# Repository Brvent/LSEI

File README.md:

# LSEI
Aquest projecte tracta de dissenyar i implementar un controlador de motor ESR

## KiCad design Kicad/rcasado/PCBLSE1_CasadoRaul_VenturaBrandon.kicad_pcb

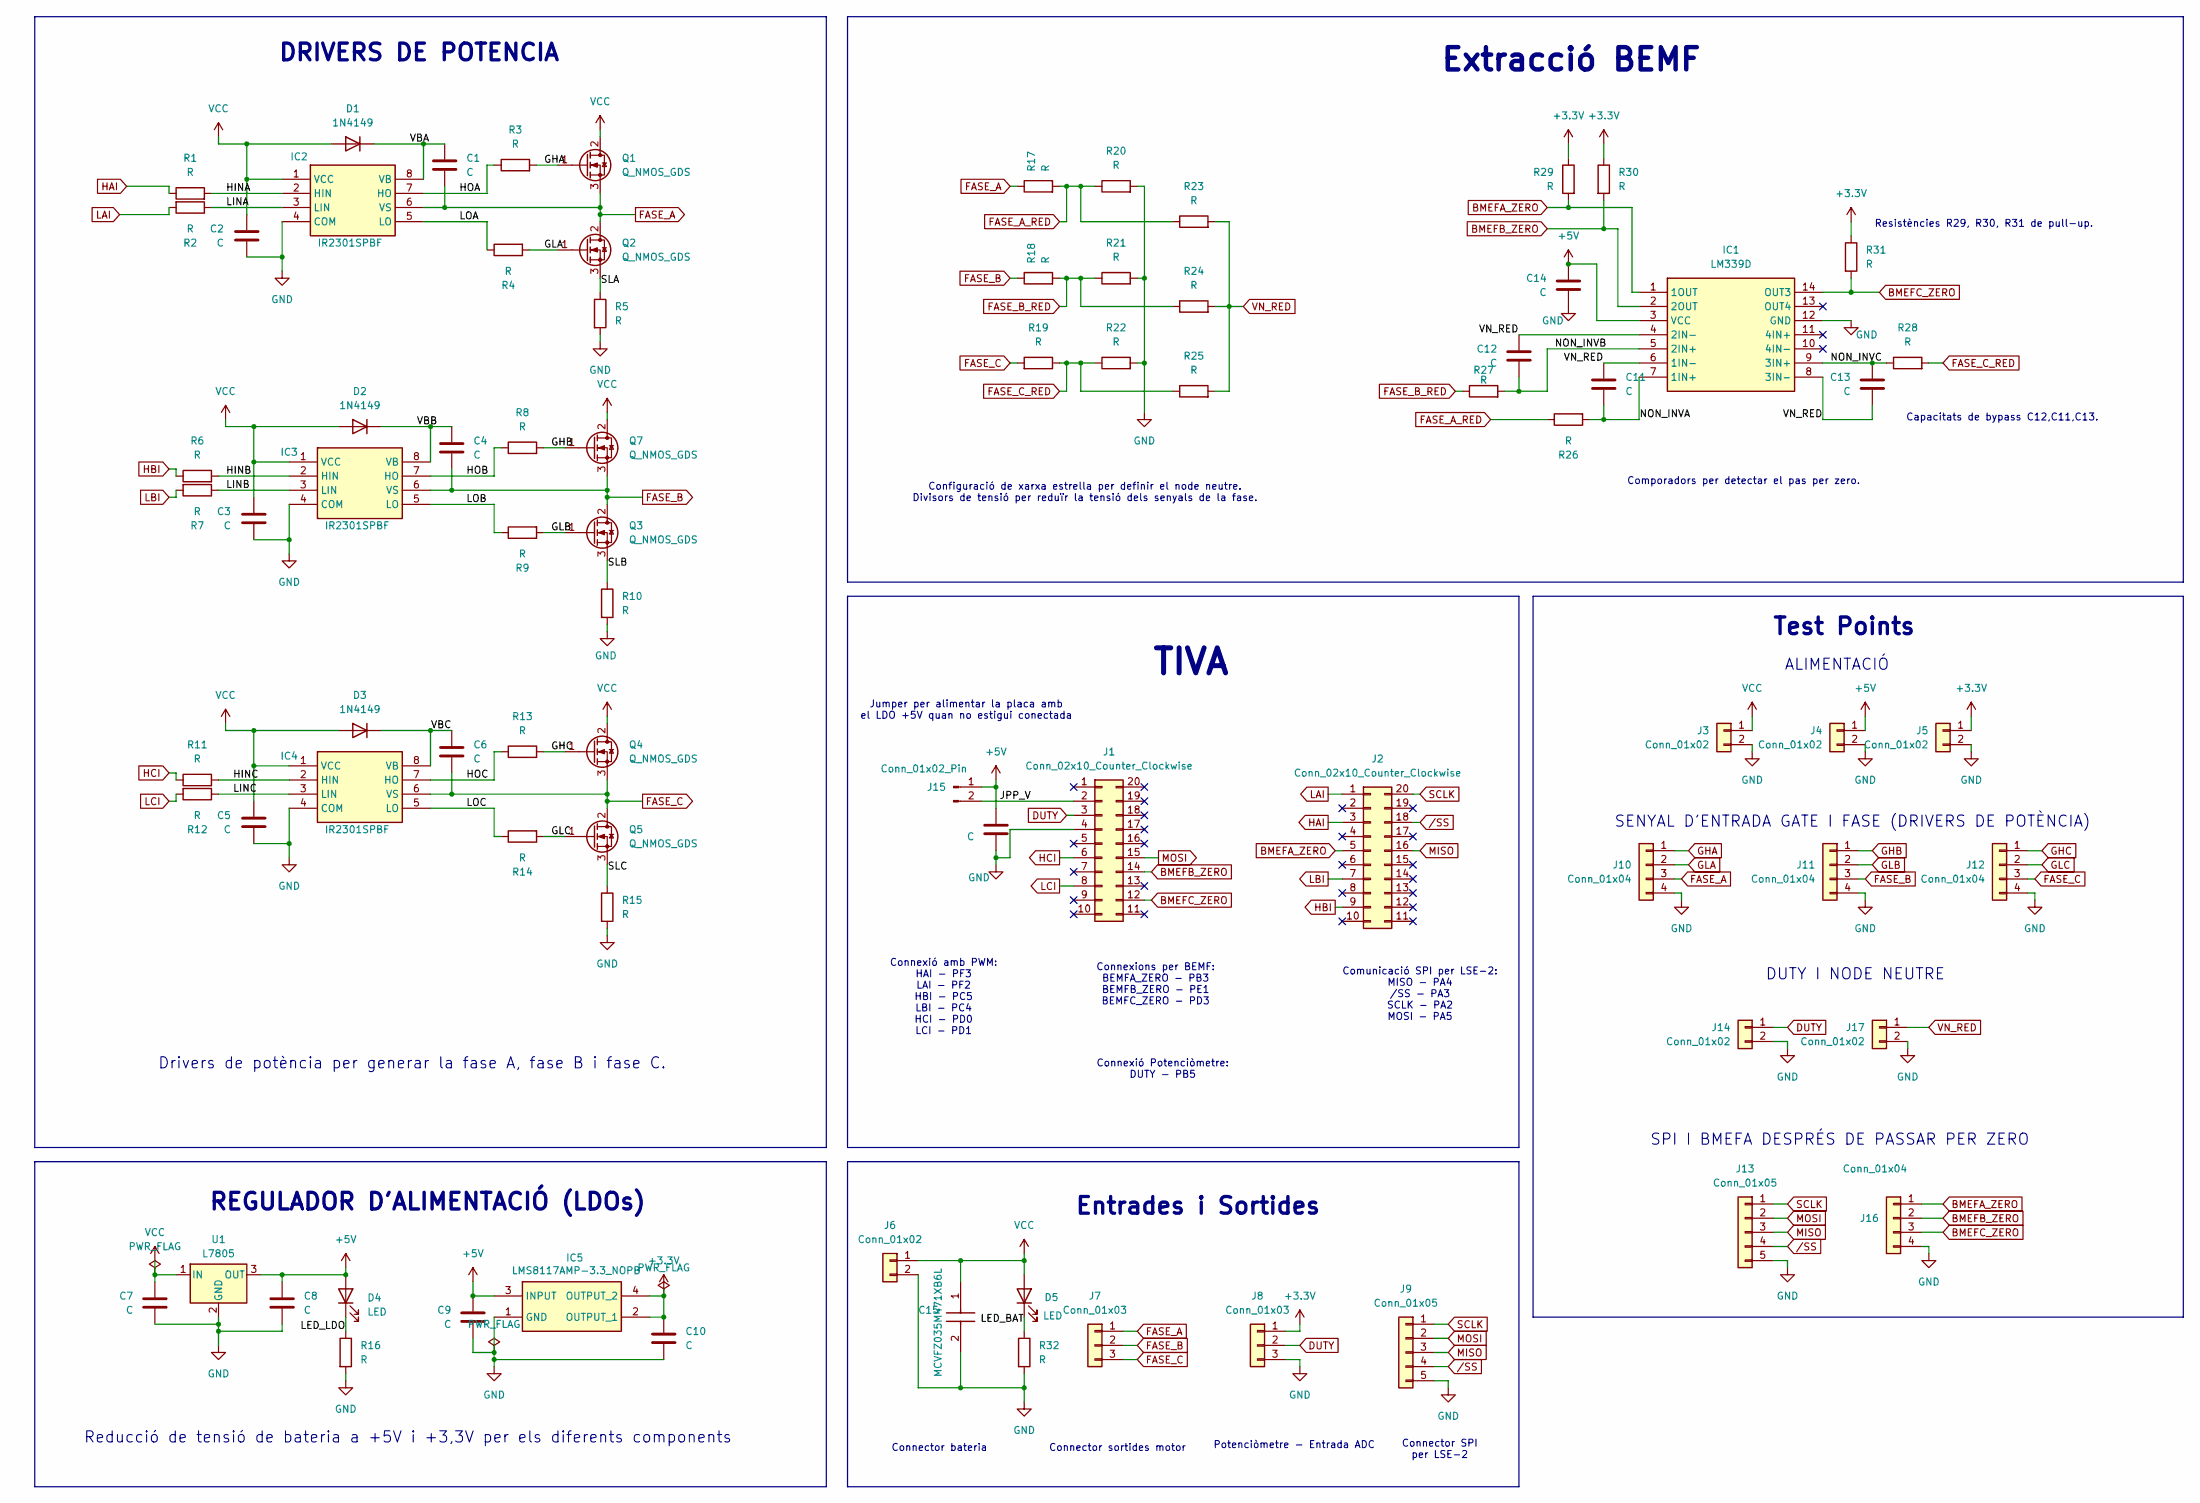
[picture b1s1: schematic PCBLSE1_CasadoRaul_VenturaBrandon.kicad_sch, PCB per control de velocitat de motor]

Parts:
C1, C2, C3, C4, C5, C6, C7, C8, C9, C10, C11, C12, C13, C14, C16: C; C_1206_3216Metric
C15: MCVFZ035M471XB6L; CAPAE1280X1300N; Manufacturer_Part_Number MCVFZ035M471XB6L
D1, D2, D3: 1N4149; D_DO-35_SOD27_P7.62mm_Horizontal
D4, D5: LED; LTL4221N
IC1: LM339D; SOIC127P600X175-14N; Mouser Part Number 595-LM339D
IC2, IC3, IC4: IR2301SPBF; SOIC127P600X175-8N; Mouser Part Number 942-IR2301SPBF
IC5: LMS8117AMP-3.3_NOPB; SOT230P700X180-4N; Mouser Part Number 926-LMS8117AMP33NOPB
J1, J2: Conn_02x10_Counter_Clockwise; PinHeader_2x10_P2.54mm_Vertical
J3, J4, J5, J14, J17: Conn_01x02; PinSocket_1x02_P2.54mm_Vertical
J6: Conn_01x02; TerminalBlock_Phoenix_MKDS-1,5-2-5.08_1x02_P5.08mm_Horizont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
J7: Conn_01x03; TerminalBlock_Phoenix_MKDS-1,5-3-5.08_1x03_P5.08mm_Horizont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
J8: Conn_01x03; PinSocket_1x03_P2.54mm_Vertical
J9, J13: Conn_01x05; PinSocket_1x05_P2.54mm_Vertical
J10, J11, J12, J16: Conn_01x04; PinSocket_1x04_P2.54mm_Vertical
J15: Conn_01x02_Pin; PinSocket_1x02_P2.54mm_Vertical
Q1, Q2, Q3, Q4, Q5, Q7: Q_NMOS_GDS; TO-252-2
R1, R2, R3, R4, R5, R6, R7, R8, R9, R10, R11, R12, R13, R14, R15, R16, R17, R18, R19, R20, R21, R22, R23, R24, R25, R26, R27, R28, R29, R30, R31, R32: R; R_1206_3216Metric
U1: L7805; TO255P460X1020X2008-3P

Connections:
+3.3V: C10.1, IC5.2 (OUTPUT_1), IC5.4 (OUTPUT_2), J5.1, J8.1, R29.1, R30.1, R31.1
+5V: C8.1, C9.1, C14.1, C16.1, D4.2 (A), IC1.3 (VCC), IC5.3 (INPUT), J4.1, J15.1, U1.3 (OUT)
/HINA: IC2.2 (HIN), R1.2
/HINB: IC3.2 (HIN), R6.2
/HINC: IC4.2 (HIN), R11.2
/HOA: IC2.7 (HO), R3.1
/HOB: IC3.7 (HO), R8.1
/HOC: IC4.7 (HO), R13.1
/JPP_V: J1.2, J15.2
/LED_BAT: D5.1 (K), R32.1
/LED_LDO: D4.1 (K), R16.1
/LINA: IC2.3 (LIN), R2.1
/LINB: IC3.3 (LIN), R7.1
/LINC: IC4.3 (LIN), R12.1
/LOA: IC2.5 (LO), R4.1
/LOB: IC3.5 (LO), R9.1
/LOC: IC4.5 (LO), R14.1
/NON_INVA: C11.2, IC1.7 (1IN+), R26.2
/NON_INVB: C12.2, IC1.5 (2IN+), R27.2
/NON_INVC: C13.1, IC1.9 (3IN+), R28.1
/SLA: Q2.3 (S), R5.1
/SLB: Q3.3 (S), R10.1
/SLC: Q5.3 (S), R15.1
/VBA: C1.1, D1.1 (K), IC2.8 (VB)
/VBB: C4.1, D2.1 (K), IC3.8 (VB)
/VBC: C6.1, D3.1 (K), IC4.8 (VB)
BMEFA_ZERO: IC1.1 (1OUT), J2.5, J16.1, R29.2
BMEFB_ZERO: IC1.2 (2OUT), J1.14, J16.2, R30.2
BMEFC_ZERO: IC1.14 (OUT3), J1.12, J16.3, R31.2
DUTY: J1.3, J8.2, J14.1
FASE_A: C1.2, IC2.6 (VS), J7.1, J10.3, Q1.3 (S), Q2.2 (D), R17.1
FASE_A_RED: R17.2, R20.1, R23.1, R26.1
FASE_B: C4.2, IC3.6 (VS), J7.2, J11.3, Q3.2 (D), Q7.3 (S), R18.1
FASE_B_RED: R18.2, R21.1, R24.1, R27.1
FASE_C: C6.2, IC4.6 (VS), J7.3, J12.3, Q4.3 (S), Q5.2 (D), R19.2
FASE_C_RED: R19.1, R22.1, R25.1, R28.2
GHA: J10.1, Q1.1 (G), R3.2
GHB: J11.1, Q7.1 (G), R8.2
GHC: J12.1, Q4.1 (G), R13.2
GLA: J10.2, Q2.1 (G), R4.2
GLB: J11.2, Q3.1 (G), R9.2
GLC: J12.2, Q5.1 (G), R14.2
GND: C2.2, C3.2, C5.2, C7.2, C8.2, C9.2, C10.2, C14.2, C15.2 (-), C16.2, IC1.12 (GND), IC2.4 (COM), IC3.4 (COM), IC4.4 (COM), IC5.1 (GND), J1.4, J3.2, J4.2, J5.2, J6.2, J8.3, J9.5, J10.4, J11.4, J12.4, J13.5, J14.2, J16.4, J17.2, R5.2, R10.2, R15.2, R16.2, R20.2, R21.2, R22.2, R32.2, U1.2 (GND)
HAI: J2.3, R1.1
HBI: J2.9, R6.1
HCI: J1.6, R11.1
LAI: J2.1, R2.2
LBI: J2.7, R7.2
LCI: J1.8, R12.2
MISO: J2.16, J9.3, J13.3
MOSI: J1.15, J9.2, J13.2
SCLK: J2.20, J9.1, J13.1
VCC: C2.1, C3.1, C5.1, C7.1, C15.1 (+), D1.2 (A), D2.2 (A), D3.2 (A), D5.2 (A), IC2.1 (VCC), IC3.1 (VCC), IC4.1 (VCC), J3.1, J6.1, Q1.2 (D), Q4.2 (D), Q7.2 (D), U1.1 (IN)
VN_RED: C11.1, C12.1, C13.2, IC1.4 (2IN-), IC1.6 (1IN-), IC1.8 (3IN-), J17.1, R23.2, R24.2, R25.2
/SS: J2.18, J9.4, J13.4

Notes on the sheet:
Capacitats de bypass C12,C11,C13.
DRIVERS DE POTENCIA
Extracció BEMF
REGULADOR D'ALIMENTACIÓ (LDOs)
Drivers de potència per generar la fase A, fase B i fase C.
Potenciòmetre - Entrada ADC
Connector SPI per LSE-2
Jumper per alimentar la placa amb el LDO +5V quan no estigui conectada
Connexió Potenciòmetre: DUTY - PB5
Configuració de xarxa estrella per definir el node neutre. Divisors de tensió per reduïr la tensió dels senyals de la fase.
DUTY I NODE NEUTRE
SENYAL D'ENTRADA GATE I FASE (DRIVERS DE POTÈNCIA)
Comporadors per detectar el pas per zero.
SPI I BMEFA DESPRÉS DE PASSAR PER ZERO
Resistències R29, R30, R31 de pull-up.
Entrades i Sortides
Connexió amb PWM: HAI - PF3 LAI - PF2 HBI - PC5 LBI - PC4 HCI - PD0 LCI - PD1
Reducció de tensió de bateria a +5V i +3,3V per els diferents components
Connector bateria
ALIMENTACIÓ
Connexions per BEMF: BEMFA_ZERO - PB3 BEMFB_ZERO - PE1 BEMFC_ZERO - PD3
Test Points
TIVA
Comunicació SPI per LSE-2: MISO - PA4 /SS - PA3 SCLK - PA2 MOSI - PA5
Connector sortides motor

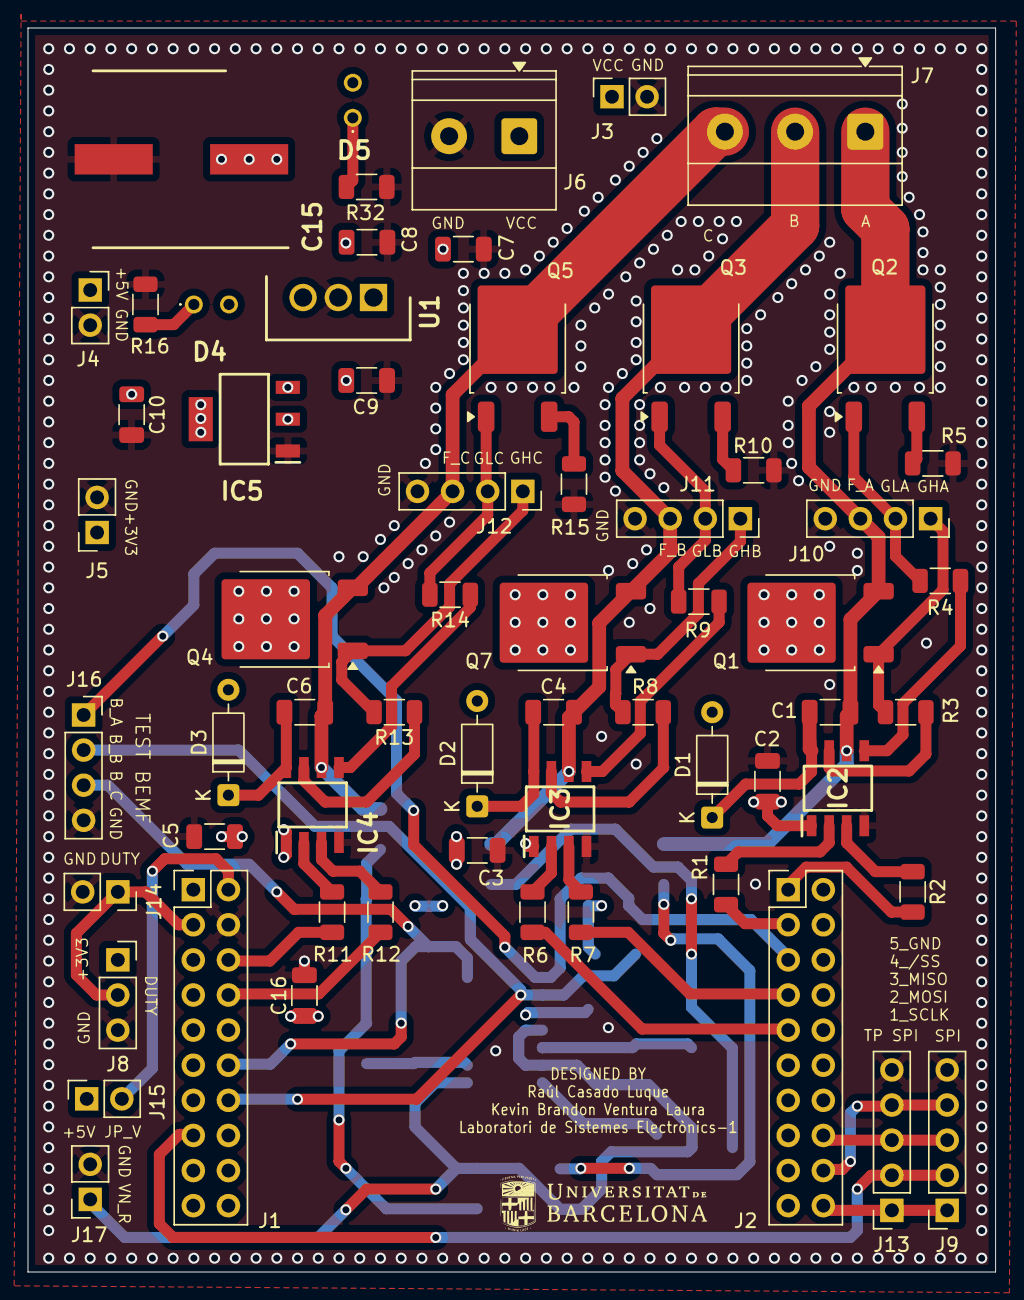
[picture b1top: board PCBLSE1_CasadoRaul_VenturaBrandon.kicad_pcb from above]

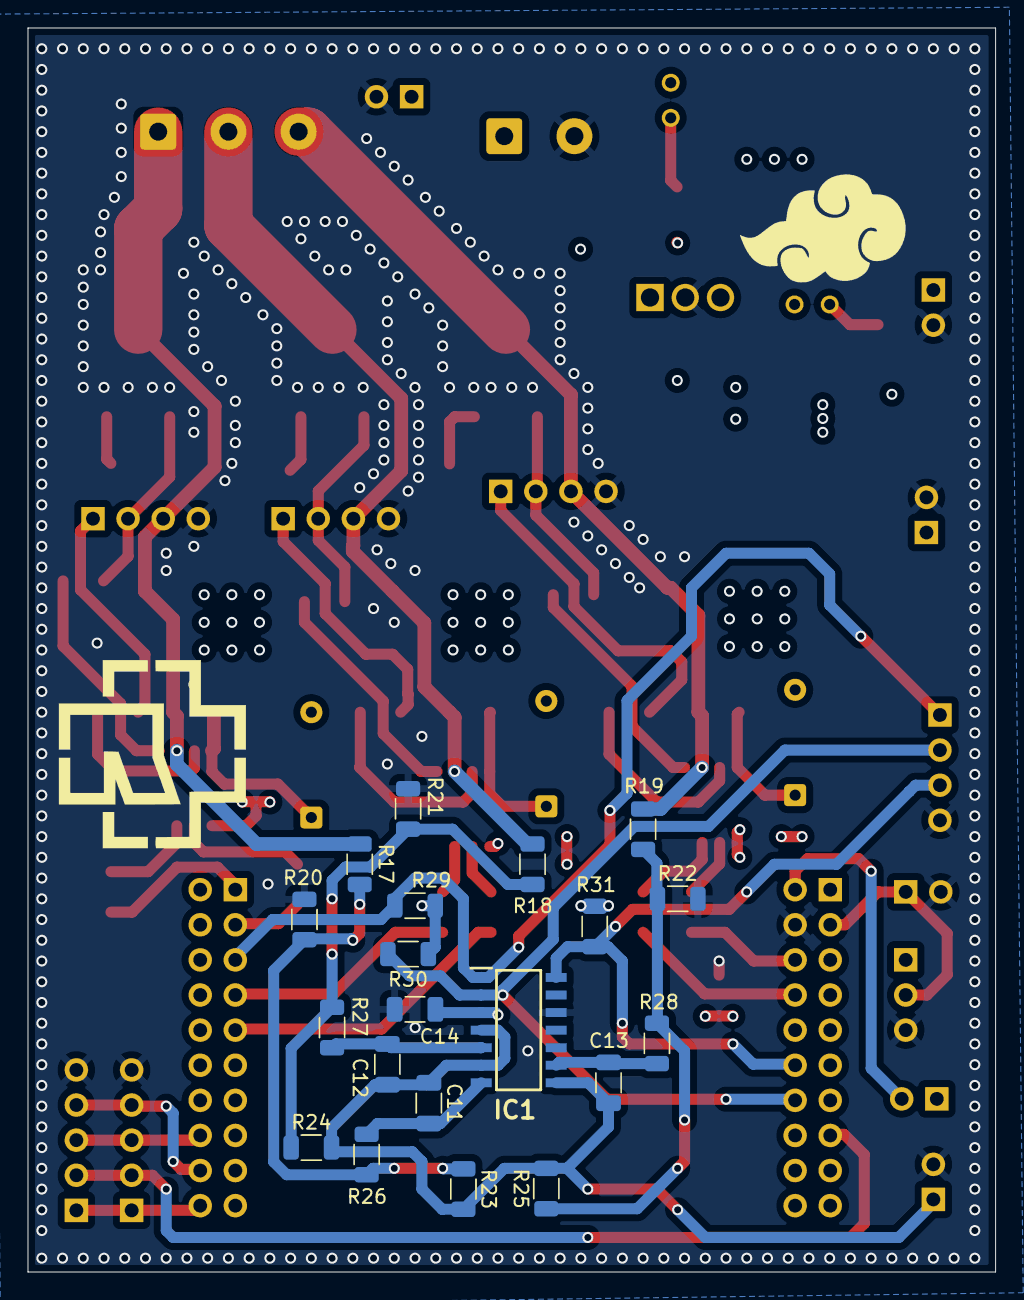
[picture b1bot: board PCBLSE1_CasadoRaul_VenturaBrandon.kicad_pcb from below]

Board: 4 copper layers, 70.0 x 90.0 mm, 82 parts (20 on the bottom side), 55 nets.

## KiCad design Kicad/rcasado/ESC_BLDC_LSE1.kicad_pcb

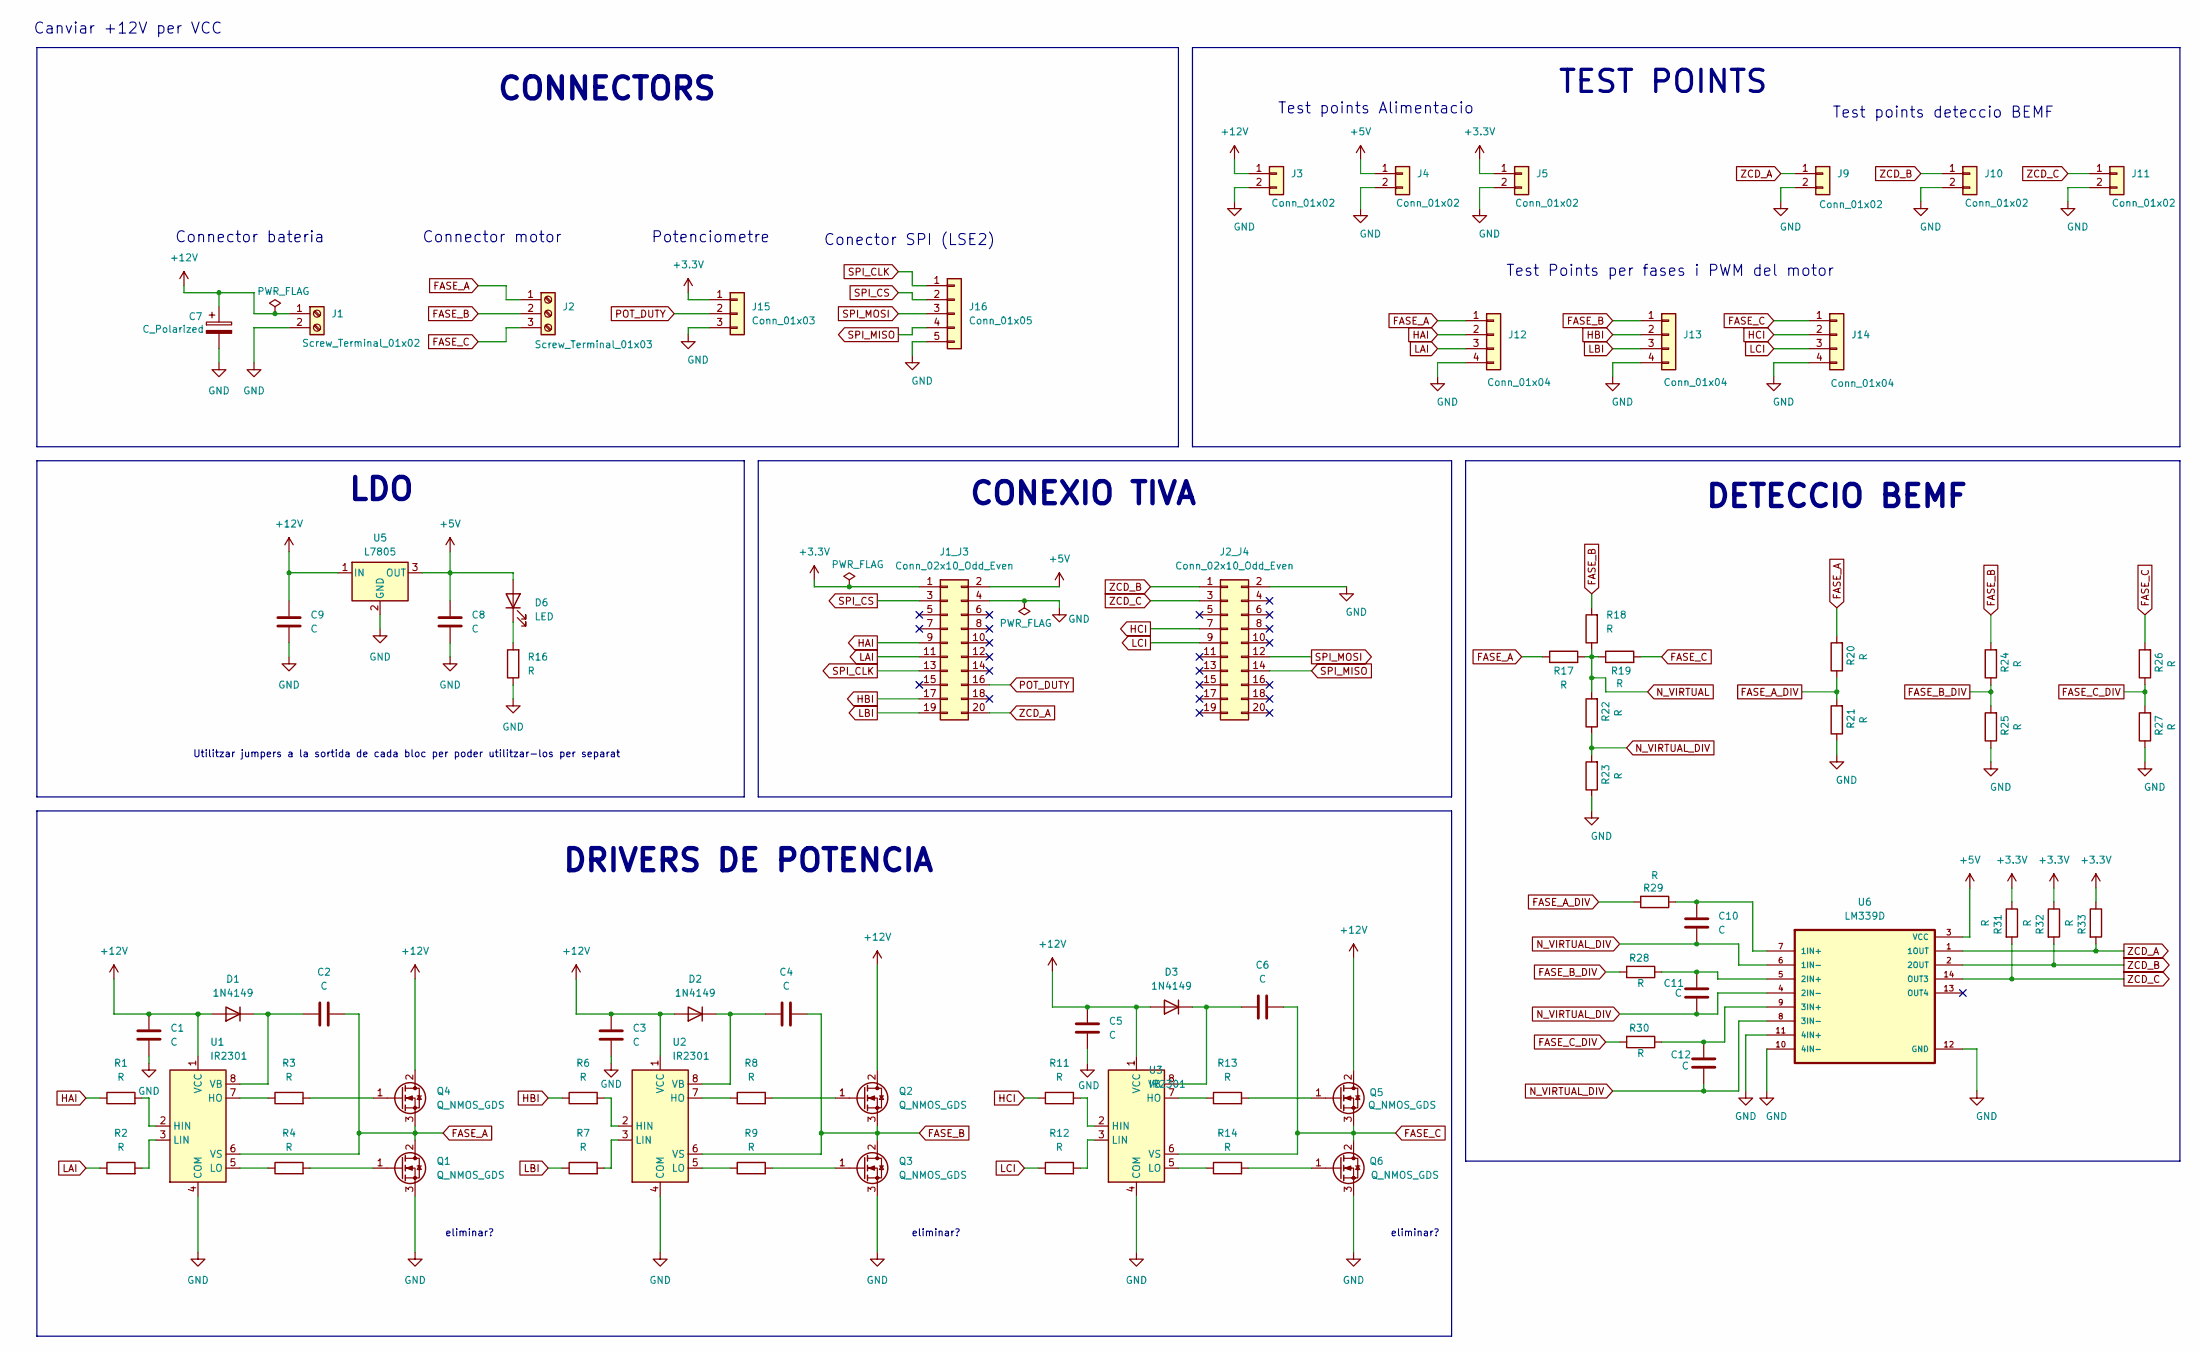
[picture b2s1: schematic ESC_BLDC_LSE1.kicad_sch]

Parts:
C1, C2, C3, C4, C5, C6, C8, C9, C10, C11, C12: C; C_1206_3216Metric_Pad1.33x1.80mm_HandSolder
C7: C_Polarized; CP_Radial_D10.0mm_P5.00mm
D1, D2, D3: 1N4149; D_DO-35_SOD27_P7.62mm_Horizontal
D6: LED; LED_D3.0mm
J1: Screw_Terminal_01x02; TerminalBlock_Phoenix_MKDS-1,5-2-5.08_1x02_P5.08mm_Horizont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
J1_J3, J2_J4: Conn_02x10_Odd_Even; PinSocket_2x10_P2.54mm_Vertical
J2: Screw_Terminal_01x03; TerminalBlock_Phoenix_MKDS-1,5-3-5.08_1x03_P5.08mm_Horizont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
J3, J4, J5, J9, J10, J11: Conn_01x02; PinHeader_1x02_P2.54mm_Vertical
J12, J13, J14: Conn_01x04; PinHeader_1x04_P2.54mm_Vertical
J15: Conn_01x03; PinHeader_1x03_P2.54mm_Vertical
J16: Conn_01x05; PinHeader_1x05_P2.54mm_Vertical
Q1, Q2, Q3, Q4, Q5, Q6: Q_NMOS_GDS; TO-252-2
R1, R2, R3, R4, R6, R7, R8, R9, R11, R12, R13, R14, R16, R17, R18, R19, R20, R21, R22, R23, R24, R25, R26, R27, R28, R29, R30, R31, R32, R33: R; R_1206_3216Metric_Pad1.30x1.75mm_HandSolder
U1, U2, U3: IR2301; SOIC-8_3.9x4.9mm_P1.27mm
U5: L7805; TO-252-3_TabPin2
U6: LM339D; SOIC127P600X175-14N

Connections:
+3.3V: J1_J3.1, J5.1, J15.1, R31.1, R32.1, R33.1
+5V: C8.2, D6.2 (A), J1_J3.2, J4.1, U5.3 (OUT), U6.3 (VCC)
+12V: C1.1, C3.1, C5.1, C7.1, C9.2, D1.2 (A), D2.2 (A), D3.2 (A), J1.1, J3.1, Q2.2 (D), Q4.2 (D), Q5.2 (D), U1.1 (VCC), U2.1 (VCC), U3.1 (VCC), U5.1 (IN)
FASE_A: C2.2, J2.1, J12.1, Q1.2 (D), Q4.3 (S), R17.1, R20.2, U1.6 (VS)
FASE_A_DIV: R20.1, R21.2, R29.2
FASE_B: C4.2, J2.2, J13.1, Q2.3 (S), Q3.2 (D), R18.2, R24.2, U2.6 (VS)
FASE_B_DIV: R24.1, R25.2, R28.2
FASE_C: C6.2, J2.3, J14.1, Q5.3 (S), Q6.2 (D), R19.2, R26.2, U3.6 (VS)
FASE_C_DIV: R26.1, R27.2, R30.2
GND: C1.2, C3.2, C5.2, C7.2, C8.1, C9.1, J1.2, J1_J3.4, J2_J4.2, J3.2, J4.2, J5.2, J9.2, J10.2, J11.2, J12.4, J13.4, J14.4, J15.3, J16.5, Q1.3 (S), Q3.3 (S), Q6.3 (S), R16.1, R21.1, R23.1, R25.1, R27.1, U1.4 (COM), U2.4 (COM), U3.4 (COM), U5.2 (GND), U6.10 (4IN-), U6.11 (4IN+), U6.12 (GND)
HAI: J1_J3.9, J12.2, R1.1
HBI: J1_J3.17, J13.2, R6.1
HCI: J2_J4.7, J14.2, R11.1
LAI: J1_J3.11, J12.3, R2.1
LBI: J1_J3.19, J13.3, R7.1
LCI: J2_J4.9, J14.3, R12.1
N_VIRTUAL: R17.2, R18.1, R19.1, R22.2
N_VIRTUAL_DIV: C10.1, C11.1, C12.1, R22.1, R23.2, U6.4 (2IN-), U6.6 (1IN-), U6.8 (3IN-)
unnamed: C2.1, D1.1 (K), U1.8 (VB)
unnamed: C4.1, D2.1 (K), U2.8 (VB)
unnamed: C6.1, D3.1 (K), U3.8 (VB)
unnamed: D6.1 (K), R16.2
unnamed: Q1.1 (G), R4.2
unnamed: Q2.1 (G), R8.2
unnamed: Q3.1 (G), R9.2
unnamed: Q4.1 (G), R3.2
unnamed: Q5.1 (G), R13.2
unnamed: Q6.1 (G), R14.2
unnamed: R1.2, U1.2 (HIN)
unnamed: R3.1, U1.7 (HO)
unnamed: R2.2, U1.3 (LIN)
unnamed: R4.1, U1.5 (LO)
unnamed: R6.2, U2.2 (HIN)
unnamed: R8.1, U2.7 (HO)
unnamed: R7.2, U2.3 (LIN)
unnamed: R9.1, U2.5 (LO)
unnamed: R11.2, U3.2 (HIN)
unnamed: R13.1, U3.7 (HO)
unnamed: R12.2, U3.3 (LIN)
unnamed: R14.1, U3.5 (LO)
unnamed: C10.2, R29.1, U6.7 (1IN+)
unnamed: C11.2, R28.1, U6.5 (2IN+)
unnamed: C12.2, R30.1, U6.9 (3IN+)
POT_DUTY: J1_J3.16, J15.2
SPI_CLK: J1_J3.13, J16.1
SPI_CS: J1_J3.3, J16.2
SPI_MISO: J2_J4.14, J16.4
SPI_MOSI: J2_J4.12, J16.3
ZCD_A: J1_J3.20, J9.1, R33.2, U6.1 (1OUT)
ZCD_B: J2_J4.1, J10.1, R32.2, U6.2 (2OUT)
ZCD_C: J2_J4.3, J11.1, R31.2, U6.14 (OUT3)

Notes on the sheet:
Connector bateria
DETECCIO BEMF
Utilitzar jumpers a la sortida de cada bloc per poder utilitzar-los per separat
LDO
CONEXIO TIVA
TEST POINTS
Potenciometre
Conector SPI (LSE2)
eliminar?
CONNECTORS
Test points Alimentacio
Connector motor
Canviar +12V per VCC
DRIVERS DE POTENCIA
Test points deteccio BEMF
Test Points per fases i PWM del motor

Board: 4 copper layers, 72 parts (23 on the bottom side), 51 nets, no tracks yet.
